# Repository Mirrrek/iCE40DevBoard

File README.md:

# iCE40 DevBoard

This project was made as part of [Hack Club Arcade 2024](https://hackclub.com/arcade/).

## Warning

The current board design has not been tested and has known mistakes:
1. **R3 is placed on the wrong side of the level shifter.** Do not solder R3 on and add a 1k pullup to 3v3 on the FPGA's _CDONE_ pin (via TP4).
2. **The FPGA's _SPI\_SS_ pin is missing a pullup resistor.** Add a 10k pullup to 3v3 on the FPGA's _SPI\_SS_ pin (via TP9).

These changes will be permanently applied to the design in a future iteration.

## Hardware

All required libraries can be downloaded from [SnapEDA](https://www.snapeda.com/home/).

- **iCE5LP2K-SG48ITR** FPGA
- **10118194-0011LF** USB micro connector
- **AMS1117** 3.3V and 1.2V voltage regulators
- **AT25DN011** SPI flash
- **CCBTLV3257MPWREP** multiplexer
- **TXS0108EPWR** level shifter

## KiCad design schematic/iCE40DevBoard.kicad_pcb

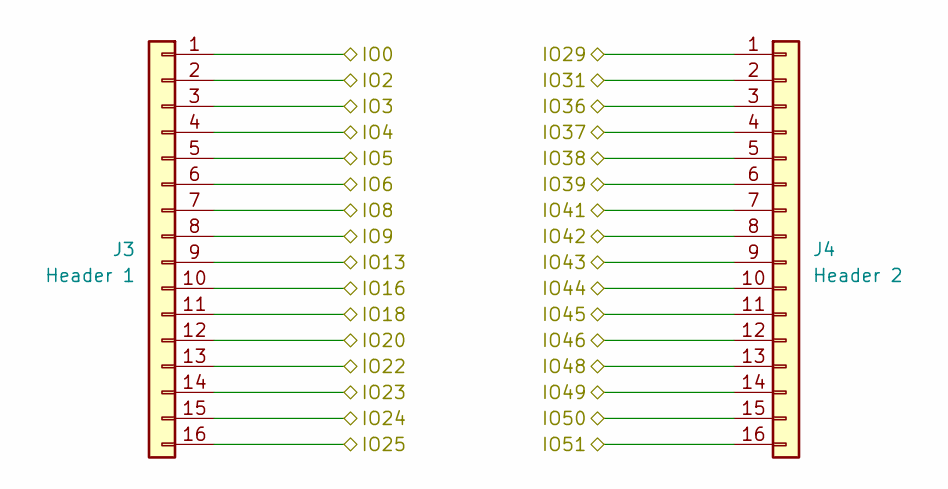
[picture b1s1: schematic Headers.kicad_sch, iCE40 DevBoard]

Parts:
J3: Header 1; PinHeader_1x16_P2.54mm_Vertical
J4: Header 2; PinHeader_1x16_P2.54mm_Vertical

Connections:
/FPGA/IO0: J3.1; also elsewhere on the board
/FPGA/IO2: J3.2; also elsewhere on the board
/FPGA/IO3: J3.3; also elsewhere on the board
/FPGA/IO4: J3.4; also elsewhere on the board
/FPGA/IO5: J3.5; also elsewhere on the board
/FPGA/IO6: J3.6; also elsewhere on the board
/FPGA/IO8: J3.7; also elsewhere on the board
/FPGA/IO9: J3.8; also elsewhere on the board
/FPGA/IO13: J3.9; also elsewhere on the board
/FPGA/IO16: J3.10; also elsewhere on the board
/FPGA/IO18: J3.11; also elsewhere on the board
/FPGA/IO20: J3.12; also elsewhere on the board
/FPGA/IO22: J3.13; also elsewhere on the board
/FPGA/IO23: J3.14; also elsewhere on the board
/FPGA/IO24: J3.15; also elsewhere on the board
/FPGA/IO25: J3.16; also elsewhere on the board
/FPGA/IO29: J4.1; also elsewhere on the board
/FPGA/IO31: J4.2; also elsewhere on the board
/FPGA/IO36: J4.3; also elsewhere on the board
/FPGA/IO37: J4.4; also elsewhere on the board
/FPGA/IO38: J4.5; also elsewhere on the board
/FPGA/IO39: J4.6; also elsewhere on the board
/FPGA/IO41: J4.7; also elsewhere on the board
/FPGA/IO42: J4.8; also elsewhere on the board
/FPGA/IO43: J4.9; also elsewhere on the board
/FPGA/IO44: J4.10; also elsewhere on the board
/FPGA/IO45: J4.11; also elsewhere on the board
/FPGA/IO46: J4.12; also elsewhere on the board
/FPGA/IO48: J4.13; also elsewhere on the board
/FPGA/IO49: J4.14; also elsewhere on the board
/FPGA/IO50: J4.15; also elsewhere on the board
/FPGA/IO51: J4.16; also elsewhere on the board

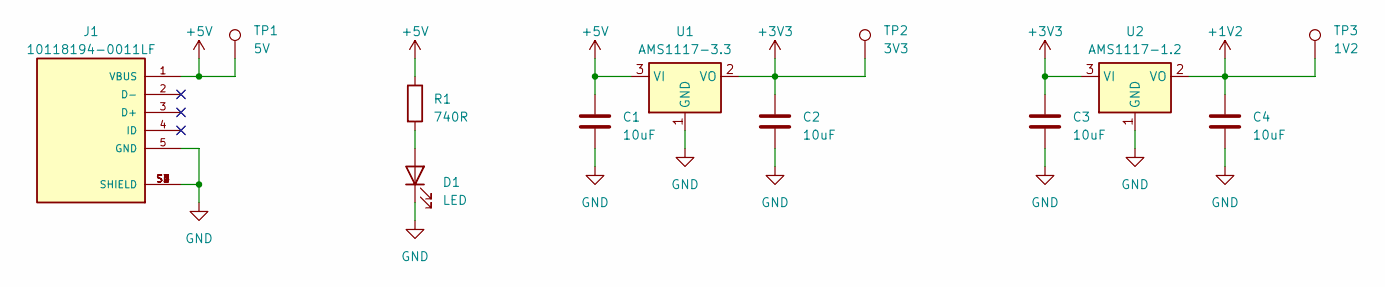
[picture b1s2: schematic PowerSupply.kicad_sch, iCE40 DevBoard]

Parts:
C1, C2, C3, C4: 10uF; C_0603_1608Metric
D1: LED; LED_0805_2012Metric
J1: 10118194-0011LF; AMPHENOL_10118194-0011LF; PARTREV D
R1: 740R; R_0603_1608Metric
TP1: 5V; TestPoint_Pad_D1.0mm
TP2: 3V3; TestPoint_Pad_D1.0mm
TP3: 1V2; TestPoint_Pad_D1.0mm
U1: AMS1117-3.3; SOT-223-3_TabPin2
U2: AMS1117-1.2; SOT-223-3_TabPin2

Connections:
+1V2: C4.1, TP3.1, U2.2 (VO); also elsewhere on the board
+3V3: C2.1, C3.1, TP2.1, U1.2 (VO), U2.3 (VI); also elsewhere on the board
+5V: C1.1, J1.1 (VBUS), R1.1, TP1.1, U1.3 (VI); also elsewhere on the board
GND: C1.2, C2.2, C3.2, C4.2, D1.1 (K), J1.5 (GND), J1.S1 (SHIELD), J1.S2 (SHIELD), J1.S3 (SHIELD), J1.S4 (SHIELD), J1.S5 (SHIELD), J1.S6 (SHIELD), U1.1 (GND), U2.1 (GND); also elsewhere on the board
unnamed: D1.2 (A), R1.2

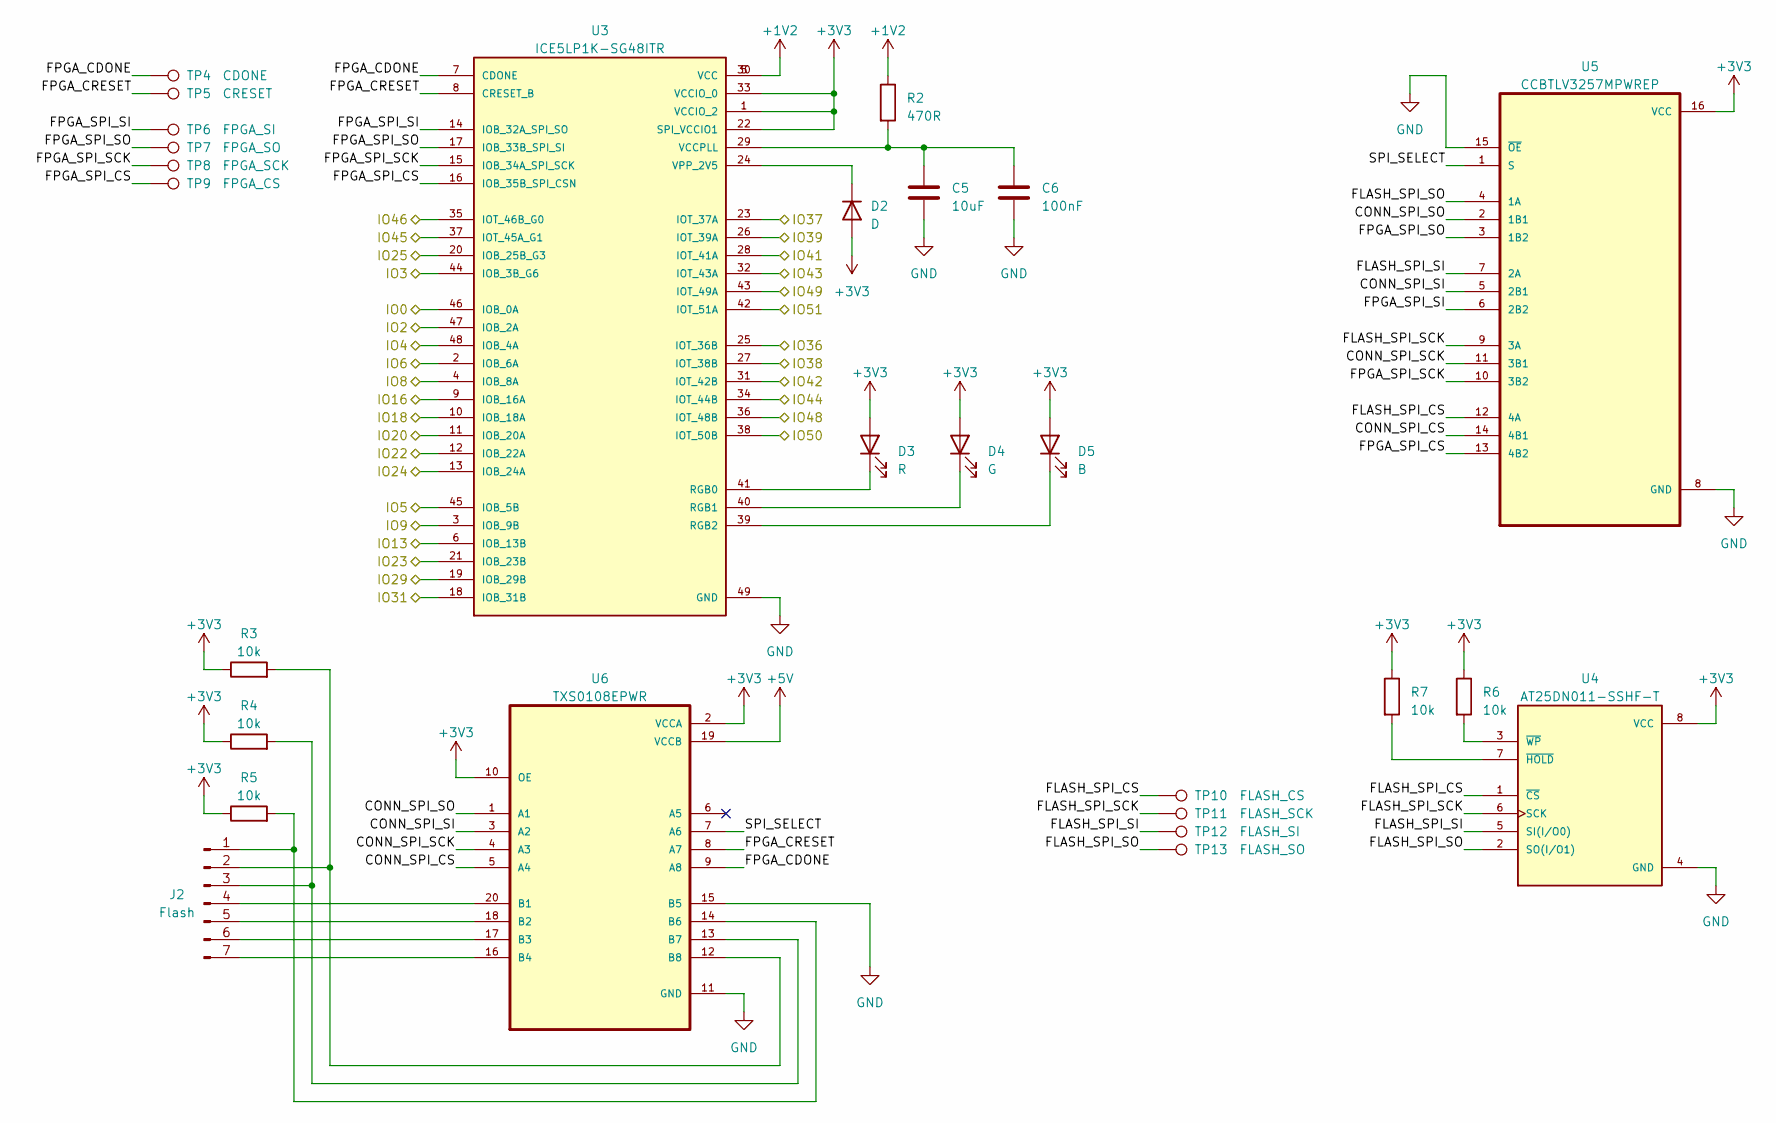
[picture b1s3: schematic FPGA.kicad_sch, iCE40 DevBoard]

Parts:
C5: 10uF; C_0603_1608Metric
C6: 100nF; C_0603_1608Metric
D2: D; D_0603_1608Metric
D3: R; LED_0805_2012Metric
D4: G; LED_0805_2012Metric
D5: B; LED_0805_2012Metric
J2: Flash; PinHeader_1x07_P2.54mm_Vertical
R2: 470R; R_0603_1608Metric
R3, R4, R5, R6, R7: 10k; R_0603_1608Metric
TP4: CDONE; TestPoint_Pad_D1.0mm
TP5: CRESET; TestPoint_Pad_D1.0mm
TP6: FPGA_SI; TestPoint_Pad_D1.0mm
TP7: FPGA_SO; TestPoint_Pad_D1.0mm
TP8: FPGA_SCK; TestPoint_Pad_D1.0mm
TP9: FPGA_CS; TestPoint_Pad_D1.0mm
TP10: FLASH_CS; TestPoint_Pad_D1.0mm
TP11: FLASH_SCK; TestPoint_Pad_D1.0mm
TP12: FLASH_SI; TestPoint_Pad_D1.0mm
TP13: FLASH_SO; TestPoint_Pad_D1.0mm
U3: ICE5LP1K-SG48ITR; QFN50P700X700X100-49N
U4: AT25DN011-SSHF-T; SOIC127P599X175-8N; PARTREV G
U5: CCBTLV3257MPWREP; SOP65P640X120-16N
U6: TXS0108EPWR; SOP65P640X120-20N

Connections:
+1V2: R2.1, U3.5 (VCC), U3.30 (VCC); also elsewhere on the board
+3V3: D2.2 (A), D3.2 (A), D4.2 (A), D5.2 (A), R3.1, R4.1, R5.1, R6.1, R7.1, U3.1 (VCCIO_2), U3.22 (SPI_VCCIO1), U3.33 (VCCIO_0), U4.8 (VCC), U5.16 (VCC), U6.2 (VCCA), U6.10 (OE); also elsewhere on the board
+5V: U6.19 (VCCB); also elsewhere on the board
/FPGA/CONN_SPI_CS: U5.14 (4B1), U6.5 (A4)
/FPGA/CONN_SPI_SCK: U5.11 (3B1), U6.4 (A3)
/FPGA/CONN_SPI_SI: U5.5 (2B1), U6.3 (A2)
/FPGA/CONN_SPI_SO: U5.2 (1B1), U6.1 (A1)
/FPGA/FLASH_SPI_CS: TP10.1, U4.1 (~CS), U5.12 (4A)
/FPGA/FLASH_SPI_SCK: TP11.1, U4.6 (SCK), U5.9 (3A)
/FPGA/FLASH_SPI_SI: TP12.1, U4.5 (SI(I/O0)), U5.7 (2A)
/FPGA/FLASH_SPI_SO: TP13.1, U4.2 (SO(I/O1)), U5.4 (1A)
/FPGA/FPGA_CDONE: TP4.1, U3.7 (CDONE), U6.9 (A8)
/FPGA/FPGA_CRESET: TP5.1, U3.8 (CRESET_B), U6.8 (A7)
/FPGA/FPGA_SPI_CS: TP9.1, U3.16 (IOB_35B_SPI_CSN), U5.13 (4B2)
/FPGA/FPGA_SPI_SCK: TP8.1, U3.15 (IOB_34A_SPI_SCK), U5.10 (3B2)
/FPGA/FPGA_SPI_SI: TP6.1, U3.14 (IOB_32A_SPI_SO), U5.6 (2B2)
/FPGA/FPGA_SPI_SO: TP7.1, U3.17 (IOB_33B_SPI_SI), U5.3 (1B2)
/FPGA/IO0: U3.46 (IOB_0A); also elsewhere on the board
/FPGA/IO2: U3.47 (IOB_2A); also elsewhere on the board
/FPGA/IO3: U3.44 (IOB_3B_G6); also elsewhere on the board
/FPGA/IO4: U3.48 (IOB_4A); also elsewhere on the board
/FPGA/IO5: U3.45 (IOB_5B); also elsewhere on the board
/FPGA/IO6: U3.2 (IOB_6A); also elsewhere on the board
/FPGA/IO8: U3.4 (IOB_8A); also elsewhere on the board
/FPGA/IO9: U3.3 (IOB_9B); also elsewhere on the board
/FPGA/IO13: U3.6 (IOB_13B); also elsewhere on the board
/FPGA/IO16: U3.9 (IOB_16A); also elsewhere on the board
/FPGA/IO18: U3.10 (IOB_18A); also elsewhere on the board
/FPGA/IO20: U3.11 (IOB_20A); also elsewhere on the board
/FPGA/IO22: U3.12 (IOB_22A); also elsewhere on the board
/FPGA/IO23: U3.21 (IOB_23B); also elsewhere on the board
/FPGA/IO24: U3.13 (IOB_24A); also elsewhere on the board
/FPGA/IO25: U3.20 (IOB_25B_G3); also elsewhere on the board
/FPGA/IO29: U3.19 (IOB_29B); also elsewhere on the board
/FPGA/IO31: U3.18 (IOB_31B); also elsewhere on the board
/FPGA/IO36: U3.25 (IOT_36B); also elsewhere on the board
/FPGA/IO37: U3.23 (IOT_37A); also elsewhere on the board
/FPGA/IO38: U3.27 (IOT_38B); also elsewhere on the board
/FPGA/IO39: U3.26 (IOT_39A); also elsewhere on the board
/FPGA/IO41: U3.28 (IOT_41A); also elsewhere on the board
/FPGA/IO42: U3.31 (IOT_42B); also elsewhere on the board
/FPGA/IO43: U3.32 (IOT_43A); also elsewhere on the board
/FPGA/IO44: U3.34 (IOT_44B); also elsewhere on the board
/FPGA/IO45: U3.37 (IOT_45A_G1); also elsewhere on the board
/FPGA/IO46: U3.35 (IOT_46B_G0); also elsewhere on the board
/FPGA/IO48: U3.36 (IOT_48B); also elsewhere on the board
/FPGA/IO49: U3.43 (IOT_49A); also elsewhere on the board
/FPGA/IO50: U3.38 (IOT_50B); also elsewhere on the board
/FPGA/IO51: U3.42 (IOT_51A); also elsewhere on the board
/FPGA/SPI_SELECT: U5.1 (S), U6.7 (A6)
GND: C5.2, C6.2, U3.49 (GND), U4.4 (GND), U5.8 (GND), U5.15 (~OE), U6.11 (GND), U6.15 (B5); also elsewhere on the board
unnamed: D2.1 (K), U3.24 (VPP_2V5)
unnamed: D3.1 (K), U3.41 (RGB0)
unnamed: D4.1 (K), U3.40 (RGB1)
unnamed: D5.1 (K), U3.39 (RGB2)
unnamed: J2.1, R5.2, U6.14 (B6)
unnamed: J2.2, R3.2, U6.12 (B8)
unnamed: J2.3, R4.2, U6.13 (B7)
unnamed: J2.4, U6.20 (B1)
unnamed: J2.5, U6.18 (B2)
unnamed: J2.6, U6.17 (B3)
unnamed: J2.7, U6.16 (B4)
unnamed: C5.1, C6.1, R2.2, U3.29 (VCCPLL)
unnamed: R7.2, U4.7 (~HOLD)
unnamed: R6.2, U4.3 (~WP)

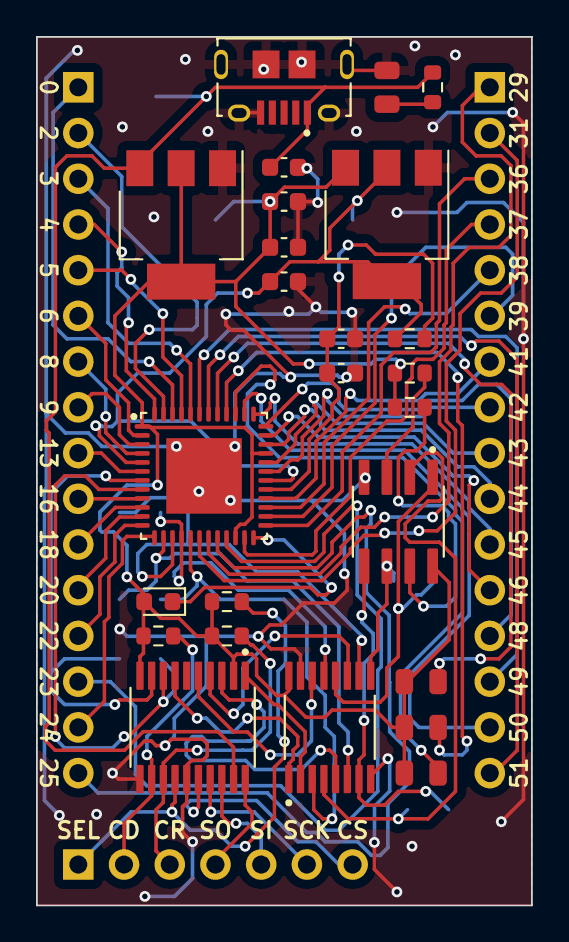
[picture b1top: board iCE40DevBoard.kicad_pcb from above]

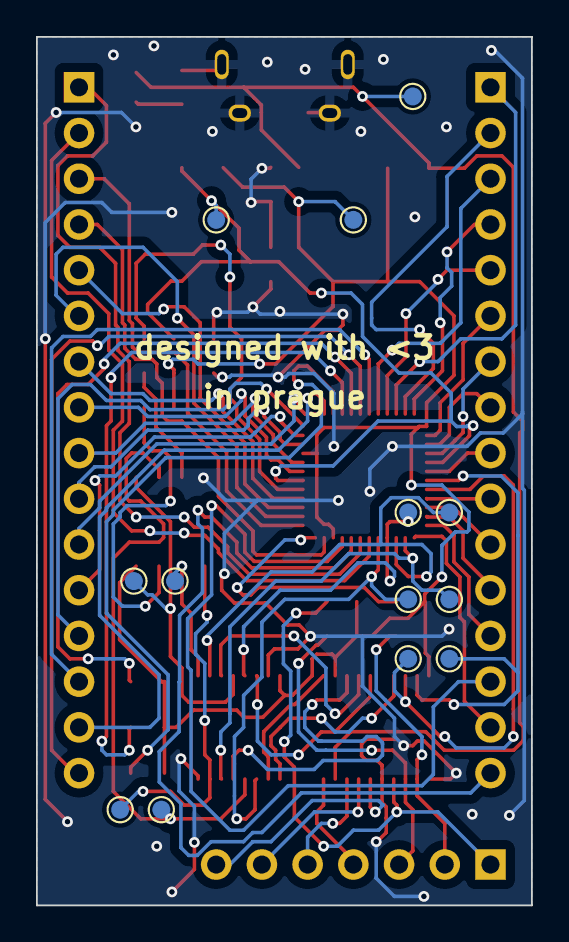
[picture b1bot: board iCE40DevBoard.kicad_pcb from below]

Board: 2 copper layers, 27.5 x 48.2 mm, 41 parts (13 on the bottom side), 66 nets.

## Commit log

2024-07-02 Initialize development environment
2024-07-02 Setup schematic
2024-07-02 Create power supply schematic
2024-07-02 Create FPGA schematic
2024-07-02 Connect FPGA to headers
2024-07-02 Add README
2024-07-02 Add level shifters to SPI lines
2024-07-02 Add testpoints to SPI lines
2024-07-02 Add RGB LEDs to schematic
2024-07-03 Update flash header schematic
2024-07-03 Design and trace PCB
2024-07-03 Generate gerber files
2024-08-12 Create flash library
2024-08-12 Replace function parameters
2024-08-12 Create interface library
2024-08-12 Fix flash address setting
2024-08-12 Add memory read command
